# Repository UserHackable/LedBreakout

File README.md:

## Led Breakouts for Arduino

These LED Breakouts are designed to be mini shields that you can simply plug into an arduino, and get to blinking those LED's right away. 

## 3MMLedBreakoutForArduino 

### Board dimensions

* (180001, 77500) original units
* (1.8000, 0.7750) inches
* (45.7203, 19.6850) mm

[gerbers](%*_gerber.zip)

| Front | Back |
| --- | --- |
|  |  |

## 5MMLedBreakoutForArduino 

### Board dimensions

* (185000, 110000) original units
* (1.8500, 1.1000) inches
* (46.9900, 27.9400) mm

[gerbers](%*_gerber.zip)

| Front | Back |
| --- | --- |
|  |  |

## OvalLedBreakoutForArduino 

### Board dimensions

* (180000, 80000) original units
* (1.8000, 0.8000) inches
* (45.7200, 20.3200) mm

[gerbers](%*_gerber.zip)

| Front | Back |
| --- | --- |
|  |  |

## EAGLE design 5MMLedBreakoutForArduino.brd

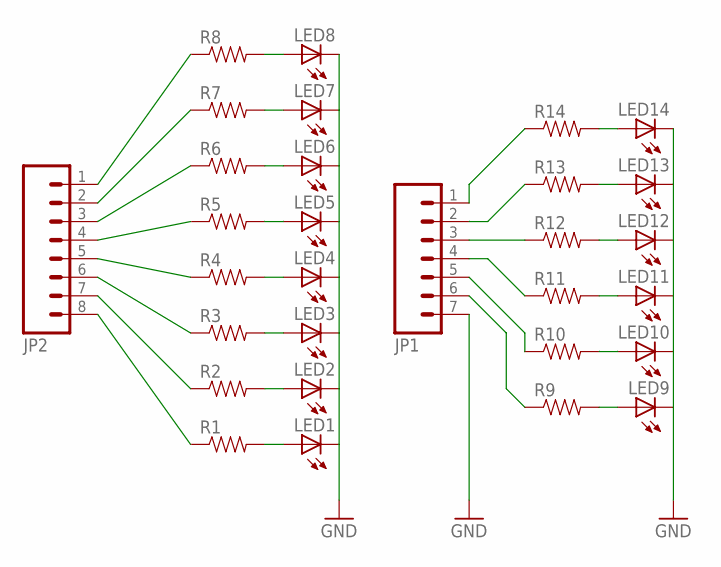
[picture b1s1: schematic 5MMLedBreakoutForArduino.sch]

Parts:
JP1: M07; 1X07
JP2: M081X08; 1X08
LED1, LED2, LED3, LED4, LED5, LED6, LED7, LED8, LED9, LED10, LED11, LED12, LED13, LED14: LED5MM
R1, R2, R3, R4, R5, R6, R7, R8, R9, R10, R11, R12, R13, R14: RESISTORAXIAL-0.3; AXIAL-0.3

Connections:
GND: JP1.7, LED1.K (C), LED2.K (C), LED3.K (C), LED4.K (C), LED5.K (C), LED6.K (C), LED7.K (C), LED8.K (C), LED9.K (C), LED10.K (C), LED11.K (C), LED12.K (C), LED13.K (C), LED14.K (C)
unnamed: LED1.A, R1.P$2 (2)
unnamed: LED2.A, R2.P$2 (2)
unnamed: LED3.A, R3.P$2 (2)
unnamed: LED4.A, R4.P$2 (2)
unnamed: LED5.A, R5.P$2 (2)
unnamed: LED6.A, R6.P$2 (2)
unnamed: LED7.A, R7.P$2 (2)
unnamed: LED8.A, R8.P$2 (2)
unnamed: LED9.A, R9.P$2 (2)
unnamed: LED10.A, R10.P$2 (2)
unnamed: LED11.A, R11.P$2 (2)
unnamed: LED12.A, R12.P$2 (2)
unnamed: LED13.A, R13.P$2 (2)
unnamed: LED14.A, R14.P$2 (2)
unnamed: JP1.1, R14.P$1 (1)
unnamed: JP1.2, R13.P$1 (1)
unnamed: JP1.3, R12.P$1 (1)
unnamed: JP1.4, R11.P$1 (1)
unnamed: JP1.5, R10.P$1 (1)
unnamed: JP1.6, R9.P$1 (1)
unnamed: JP2.1, R8.P$1 (1)
unnamed: JP2.2, R7.P$1 (1)
unnamed: JP2.3, R6.P$1 (1)
unnamed: JP2.4, R5.P$1 (1)
unnamed: JP2.5, R4.P$1 (1)
unnamed: JP2.6, R3.P$1 (1)
unnamed: JP2.7, R2.P$1 (1)
unnamed: JP2.8, R1.P$1 (1)

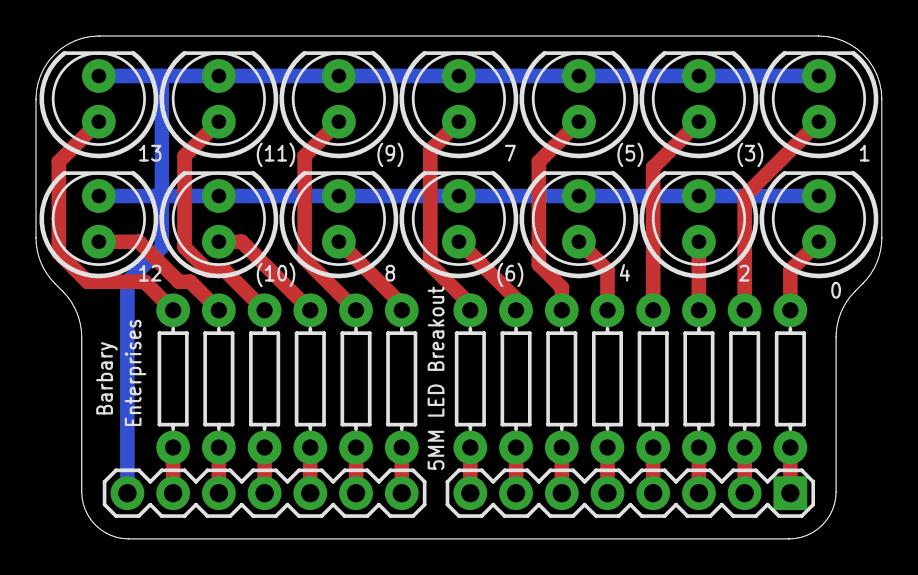
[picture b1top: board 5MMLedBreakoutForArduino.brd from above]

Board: 2 copper layers, 47.0 x 27.9 mm, 30 parts (0 on the bottom side), 29 nets.

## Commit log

2016-04-08 from Makefile

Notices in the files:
parts and their libraries:
SparkFun-Connectors: Licensing: Creative Commons ShareAlike 4.0 International - https://creativecommons.org/licenses/by-sa/4.0
